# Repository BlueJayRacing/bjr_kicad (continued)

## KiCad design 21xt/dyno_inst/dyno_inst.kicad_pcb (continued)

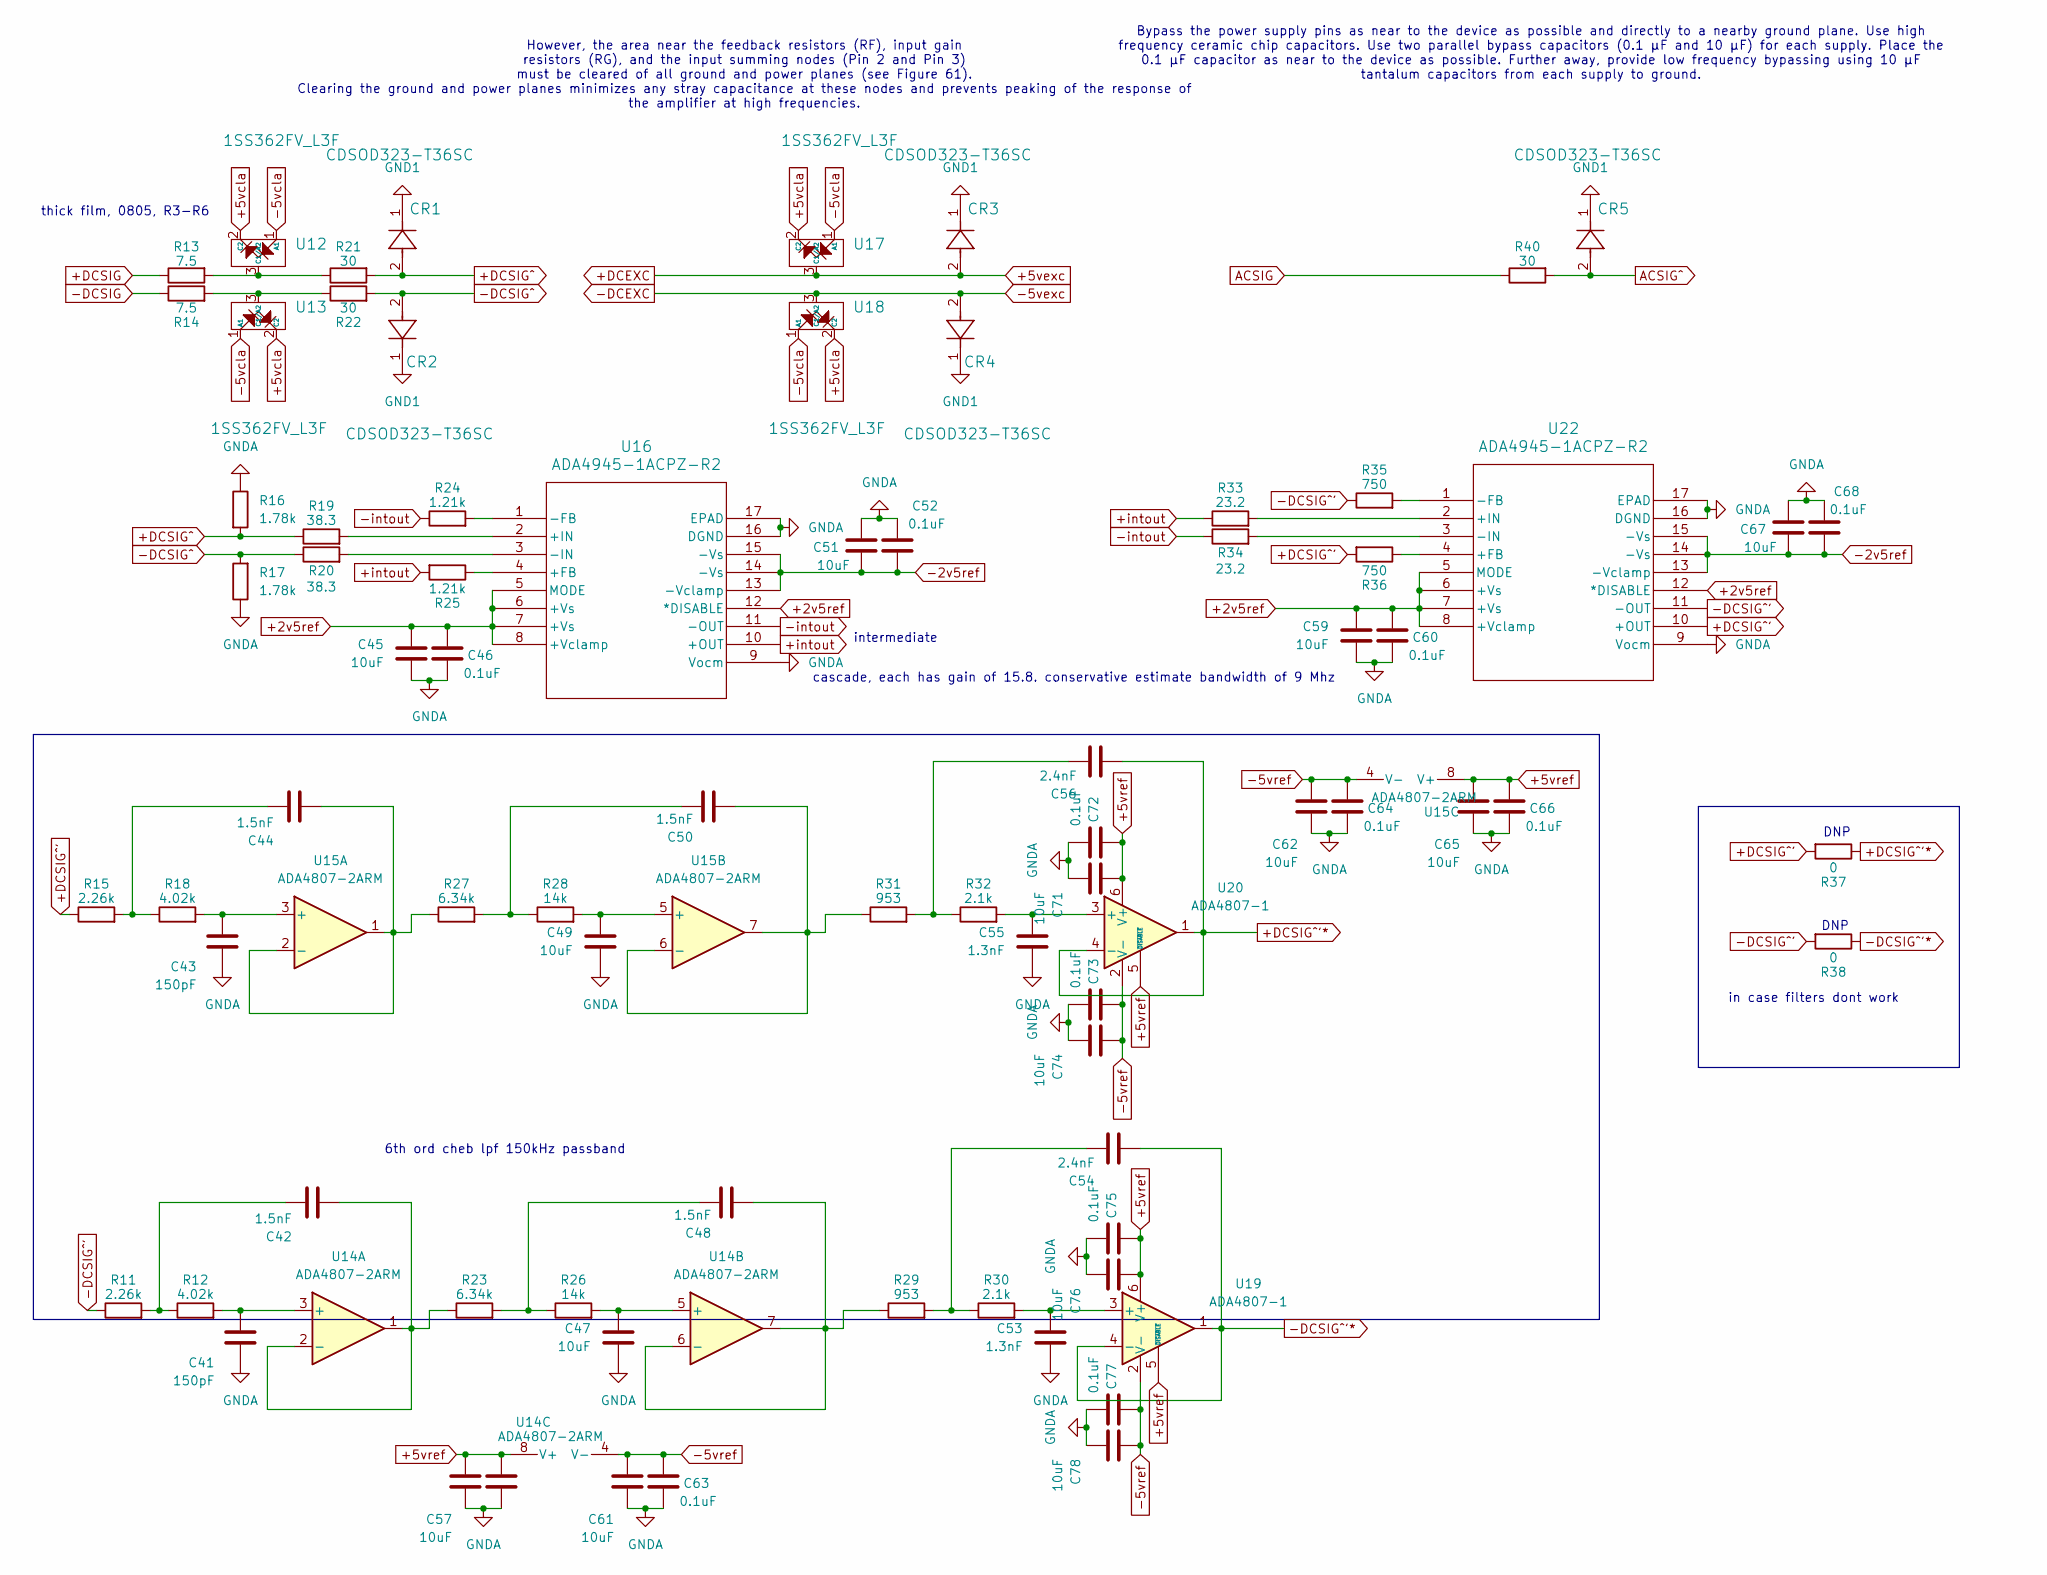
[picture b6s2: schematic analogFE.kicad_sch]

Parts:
C41, C43: 150pF; C_0402_1005Metric
C42, C44, C48, C50: 1.5nF; C_0402_1005Metric
C45, C47, C49, C51, C57, C59, C61, C62, C65, C67, C71, C74, C76, C78: 10uF; C_0402_1005Metric
C46, C52, C58, C60, C63, C64, C66, C68, C72, C73, C75, C77: 0.1uF; C_0402_1005Metric
C53, C55: 1.3nF; C_0402_1005Metric
C54, C56: 2.4nF; C_0402_1005Metric
CR1, CR2, CR3, CR4, CR5: CDSOD323-T36SC; DIODE_CDSOD323-T36SC_BRN
R11, R15: 2.26k; R_0402_1005Metric
R12, R18: 4.02k; R_0402_1005Metric
R13, R14: 7.5; R_0805_2012Metric
R16, R17: 1.78k; R_0402_1005Metric
R19, R20: 38.3; R_0402_1005Metric
R21, R22, R40: 30; R_0805_2012Metric
R23, R27: 6.34k; R_0402_1005Metric
R24, R25: 1.21k; R_0402_1005Metric
R26, R28: 14k; R_0402_1005Metric
R29, R31: 953; R_0402_1005Metric
R30, R32: 2.1k; R_0402_1005Metric
R33, R34: 23.2; R_0402_1005Metric
R35, R36: 750; R_0402_1005Metric
R37, R38: 0; R_0402_1005Metric
U12, U13, U17, U18: 1SS362FV_L3F; SOT-723
U14, U15: ADA4807-2ARM; MSOP-8_3x3mm_P0.65mm
U16, U22: ADA4945-1ACPZ-R2; LFCSP16_ADA4945-1ACPZ-R2_ADI
U19, U20: ADA4807-1; KS-6_ADI

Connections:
+2v5ref: C45.1, C46.1, C59.1, C60.1, U16.5 (MODE), U16.6 (+Vs), U16.7 (+Vs), U16.8 (+Vclamp), U16.12 (*DISABLE), U22.5 (MODE), U22.6 (+Vs), U22.7 (+Vs), U22.8 (+Vclamp), U22.12 (*DISABLE); also elsewhere on the board
+5vcla: U12.2 (C2), U13.2 (C2), U17.2 (C2), U18.2 (C2); also elsewhere on the board
+5vexc: CR3.2, U17.3 (C1/A2); also elsewhere on the board
+5vref: C57.1, C58.1, C65.1, C66.1, C71.1, C72.1, C75.1, C76.1, U14.8 (V+), U15.8 (V+), U19.5 (~DISABLE), U19.6 (V+), U20.5 (~DISABLE), U20.6 (V+); also elsewhere on the board
+DCSIG: R13.1; also elsewhere on the board
+DCSIG^: CR1.2, R16.2, R19.1, R21.2
+DCSIG^': R15.1, R36.2, R37.2, U22.10 (+OUT)
+DCSIG^'*: C56.2, R37.1, U20.1, U20.4 (-); also elsewhere on the board
+intout: R25.2, R33.1, U16.10 (+OUT)
-2v5ref: C51.2, C52.2, C67.2, C68.2, U16.13 (-Vclamp), U16.14 (-Vs), U16.15 (-Vs), U22.13 (-Vclamp), U22.14 (-Vs), U22.15 (-Vs); also elsewhere on the board
-5vcla: U12.1 (A1), U13.1 (A1), U17.1 (A1), U18.1 (A1); also elsewhere on the board
-5vexc: CR4.2, U18.3 (C1/A2); also elsewhere on the board
-5vref: C61.1, C62.1, C63.1, C64.1, C73.1, C74.1, C77.1, C78.1, U14.4 (V-), U15.4 (V-), U19.2 (V-), U20.2 (V-); also elsewhere on the board
-DCSIG: R14.1; also elsewhere on the board
-DCSIG^: CR2.2, R17.2, R20.1, R22.2
-DCSIG^': R11.1, R35.1, R38.2, U22.11 (-OUT)
-DCSIG^'*: C54.2, R38.1, U19.1, U19.4 (-); also elsewhere on the board
-intout: R24.1, R34.1, U16.11 (-OUT)
ACSIG: R40.1; also elsewhere on the board
ACSIG^: CR5.2, R40.2; also elsewhere on the board
GND1: CR1.1, CR2.1, CR3.1, CR4.1, CR5.1; also elsewhere on the board
GNDA: C41.2, C43.2, C45.2, C46.2, C47.2, C49.2, C51.1, C52.1, C53.2, C55.2, C57.2, C58.2, C59.2, C60.2, C61.2, C62.2, C63.2, C64.2, C65.2, C66.2, C67.1, C68.1, C71.2, C72.2, C73.2, C74.2, C75.2, C76.2, C77.2, C78.2, R16.1, R17.1, U16.9 (Vocm), U16.16 (DGND), U16.17 (EPAD), U22.9 (Vocm), U22.16 (DGND), U22.17 (EPAD); also elsewhere on the board
unnamed: C42.1, R11.2, R12.1
unnamed: C44.1, R15.2, R18.1
unnamed: C48.1, R23.2, R26.1
unnamed: C50.1, R27.2, R28.1
unnamed: C54.1, R29.2, R30.1
unnamed: C56.1, R31.2, R32.1
unnamed: R13.2, R21.1, U12.3 (C1/A2)
unnamed: R14.2, R22.1, U13.3 (C1/A2)
unnamed: C41.1, R12.2, U14.3 (+)
unnamed: C42.2, R23.1, U14.1, U14.2 (-)
unnamed: C47.1, R26.2, U14.5 (+)
unnamed: C48.2, R29.1, U14.6 (-), U14.7
unnamed: C43.1, R18.2, U15.3 (+)
unnamed: C44.2, R27.1, U15.1, U15.2 (-)
unnamed: C49.1, R28.2, U15.5 (+)
unnamed: C50.2, R31.1, U15.6 (-), U15.7
unnamed: R25.1, U16.4 (+FB)
unnamed: R19.2, U16.2 (+IN)
unnamed: R24.2, U16.1 (-FB)
unnamed: R20.2, U16.3 (-IN)
unnamed: C53.1, R30.2, U19.3 (+)
unnamed: C55.1, R32.2, U20.3 (+)
unnamed: R36.1, U22.4 (+FB)
unnamed: R33.2, U22.2 (+IN)
unnamed: R35.2, U22.1 (-FB)
unnamed: R34.2, U22.3 (-IN)

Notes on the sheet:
in case filters dont work
DNP
intermediate
6th ord cheb lpf 150kHz passband
However, the area near the feedback resistors (RF), input gain resistors (RG), and the input summing nodes (Pin 2 and Pin 3) must be cleared of all ground and power planes (see Figure 61). Clearing the ground and power planes minimizes any stray capacitance at these nodes and prevents peaking of th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
Bypass the power supply pins as near to the device as possible and directly to a nearby ground plane. Use high frequency ceramic chip capacitors. Use two parallel bypass capacitors (0.1 µF and 10 µF) for each supply. Place the 0.1 µF capacitor as near to the device as possible. Further away, provid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
thick film, 0805, R3-R6
cascade, each has gain of 15.8. conservative estimate bandwidth of 9 Mhz

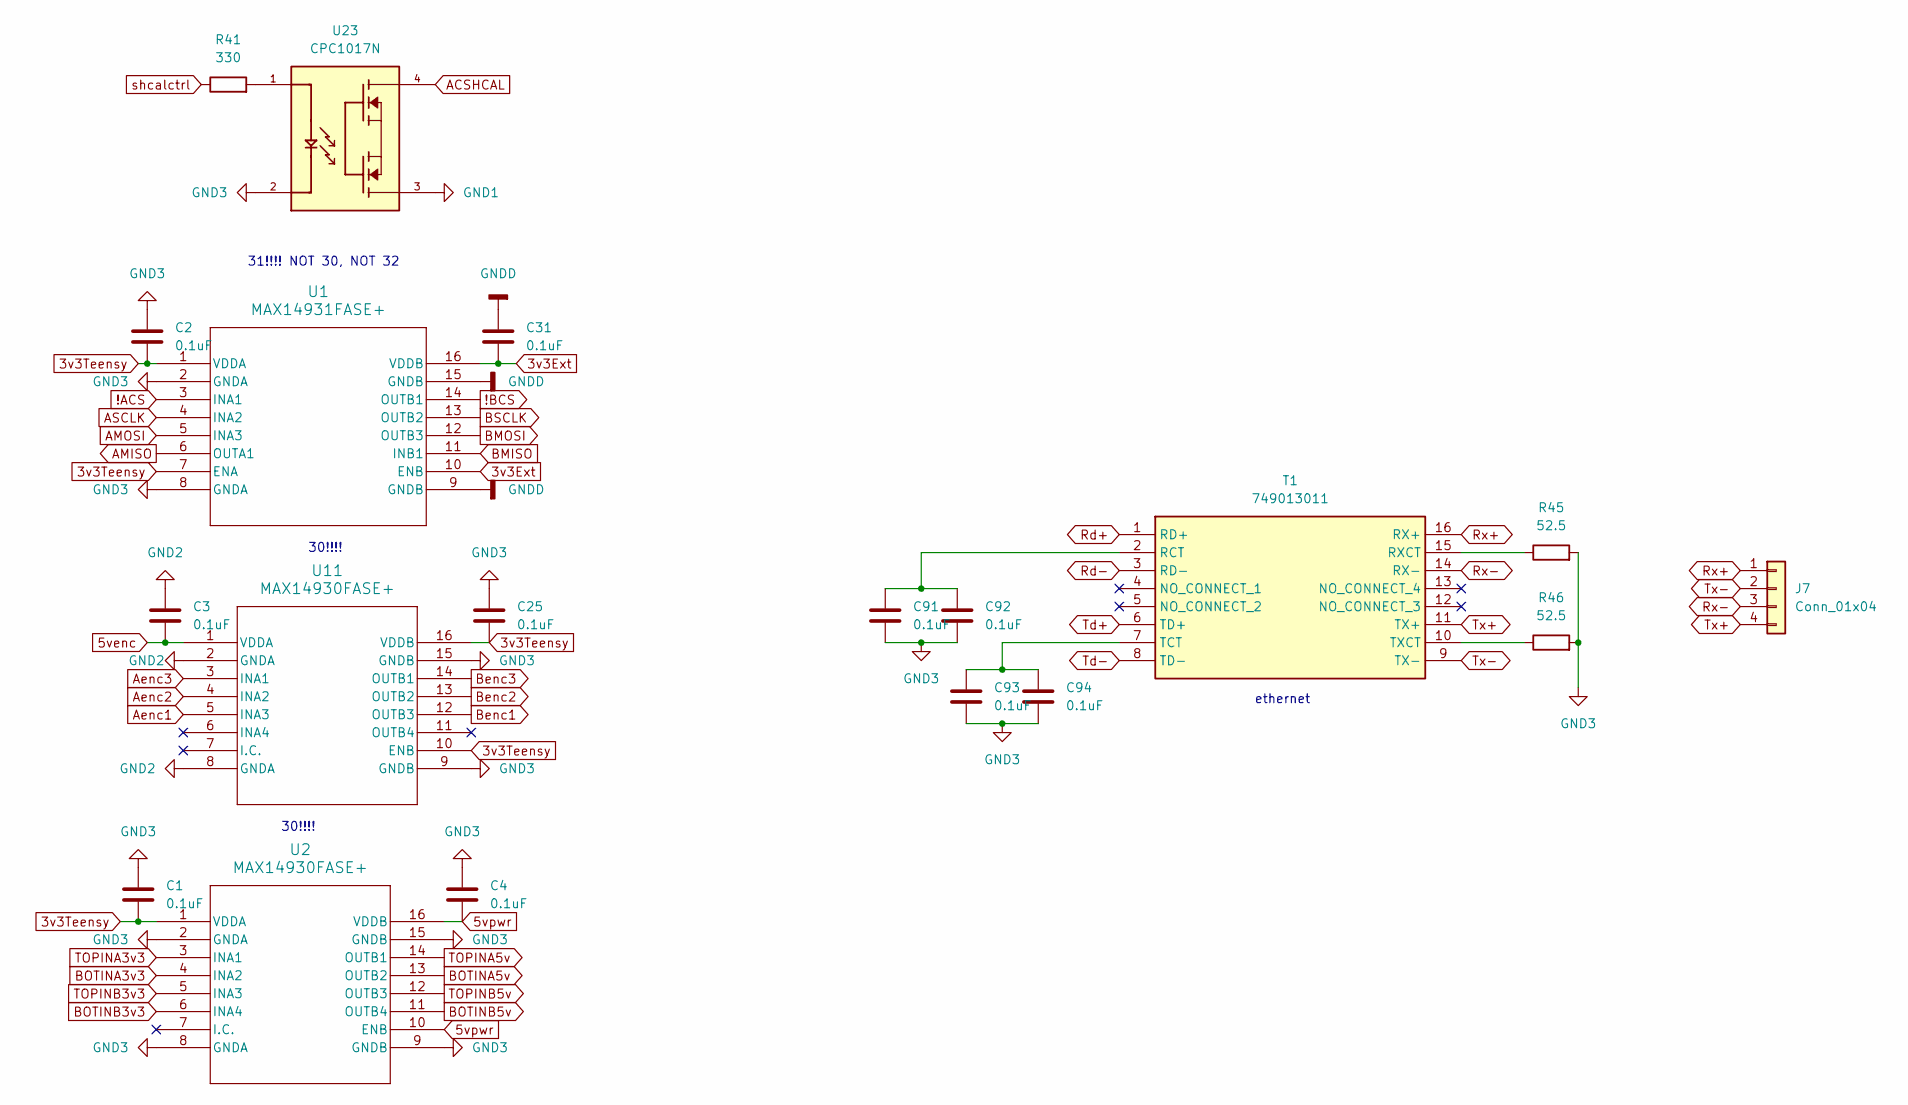
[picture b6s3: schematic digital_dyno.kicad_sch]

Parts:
C1, C2, C3, C4, C25, C31, C91, C92, C93, C94: 0.1uF; C_0402_1005Metric
J7: Conn_01x04; CONN_T4041017041-000_TEC
R41: 330; R_0402_1005Metric
R45, R46: 52.5; R_0402_1005Metric
T1: 749013011; Mouser Part Number 710-749013011
U1: MAX14931FASE+; 21-0041_S16&plus_1_MXM_1
U2, U11: MAX14930FASE+; 21-0041_S16&plus_1_MXM
U23: CPC1017N; SOIC254P610X218-4N

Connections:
3v3Ext: C31.2, U1.10 (ENB), U1.16 (VDDB); also elsewhere on the board
3v3Teensy: C1.2, C2.2, C25.2, U1.1 (VDDA), U1.7 (ENA), U2.1 (VDDA), U11.10 (ENB), U11.16 (VDDB); also elsewhere on the board
5venc: C3.2, U11.1 (VDDA); also elsewhere on the board
5vpwr: C4.2, U2.10 (ENB), U2.16 (VDDB); also elsewhere on the board
!ACS: U1.3 (INA1); also elsewhere on the board
!BCS: U1.14 (OUTB1); also elsewhere on the board
ACSHCAL: U23.4; also elsewhere on the board
AMISO: U1.6 (OUTA1); also elsewhere on the board
AMOSI: U1.5 (INA3); also elsewhere on the board
ASCLK: U1.4 (INA2); also elsewhere on the board
Aenc1: U11.5 (INA3); also elsewhere on the board
Aenc2: U11.4 (INA2); also elsewhere on the board
Aenc3: U11.3 (INA1); also elsewhere on the board
BMISO: U1.11 (INB1); also elsewhere on the board
BMOSI: U1.12 (OUTB3); also elsewhere on the board
BOTINA3v3: U2.4 (INA2); also elsewhere on the board
BOTINA5v: U2.13 (OUTB2); also elsewhere on the board
BOTINB3v3: U2.6 (INA4); also elsewhere on the board
BOTINB5v: U2.11 (OUTB4); also elsewhere on the board
BSCLK: U1.13 (OUTB2); also elsewhere on the board
Benc1: U11.12 (OUTB3); also elsewhere on the board
Benc2: U11.13 (OUTB2); also elsewhere on the board
Benc3: U11.14 (OUTB1); also elsewhere on the board
GND1: U23.3; also elsewhere on the board
GND2: C3.1, U11.2 (GNDA), U11.8 (GNDA); also elsewhere on the board
GND3: C1.1, C2.1, C4.1, C25.1, C91.2, C92.2, C93.2, C94.2, R45.2, R46.2, U1.2 (GNDA), U1.8 (GNDA), U2.2 (GNDA), U2.8 (GNDA), U2.9 (GNDB), U2.15 (GNDB), U11.9 (GNDB), U11.15 (GNDB), U23.2; also elsewhere on the board
GNDD: C31.1, U1.9 (GNDB), U1.15 (GNDB); also elsewhere on the board
unnamed: R41.2, U23.1
unnamed: C91.1, C92.1, T1.2 (RCT)
unnamed: R45.1, T1.15 (RXCT)
unnamed: C93.1, C94.1, T1.7 (TCT)
unnamed: R46.1, T1.10 (TXCT)
Rd+: T1.1 (RD+); also elsewhere on the board
Rd-: T1.3 (RD-); also elsewhere on the board
Rx+: J7.1, T1.16 (RX+)
Rx-: J7.3, T1.14 (RX-)
TOPINA3v3: U2.3 (INA1); also elsewhere on the board
TOPINA5v: U2.14 (OUTB1); also elsewhere on the board
TOPINB3v3: U2.5 (INA3); also elsewhere on the board
TOPINB5v: U2.12 (OUTB3); also elsewhere on the board
Td+: T1.6 (TD+); also elsewhere on the board
Td-: T1.8 (TD-); also elsewhere on the board
Tx+: J7.4, T1.11 (TX+)
Tx-: J7.2, T1.9 (TX-)
shcalctrl: R41.1; also elsewhere on the board

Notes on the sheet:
31!!!! NOT 30, NOT 32
30!!!!
ethernet

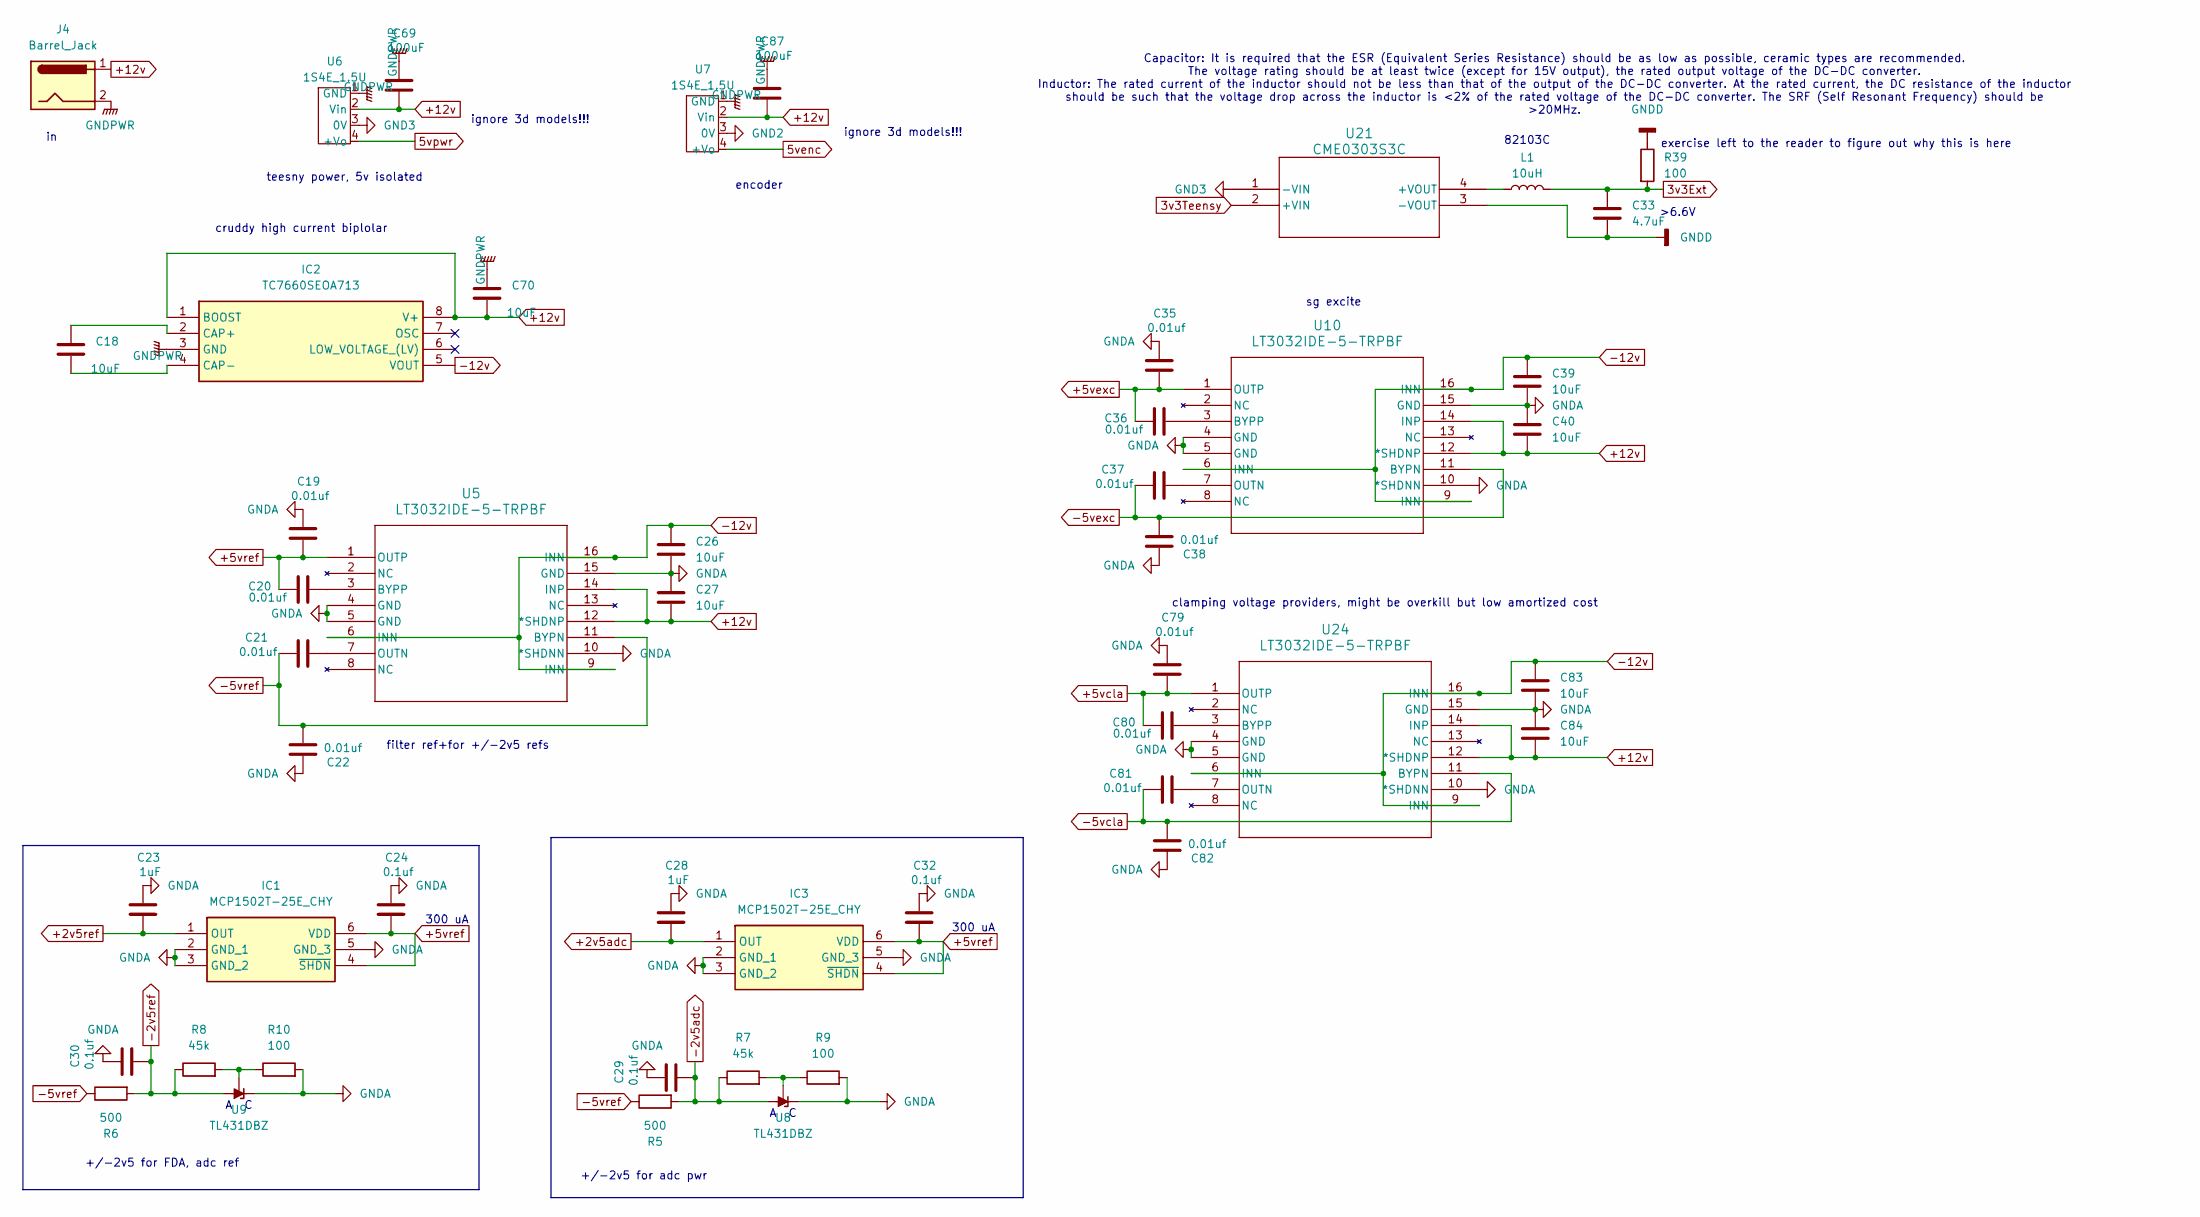
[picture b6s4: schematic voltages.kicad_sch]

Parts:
C18, C70: 10uF; C_0603_1608Metric
C19, C20, C21, C22, C35, C36, C37, C38, C79, C80, C81, C82: 0.01uf; C_0402_1005Metric
C23, C28: 1uF; C_0402_1005Metric
C24, C29, C30, C32: 0.1uf; C_0402_1005Metric
C26, C27, C39, C40, C83, C84: 10uF; C_0402_1005Metric
C33: 4.7uF; C_0402_1005Metric
C69, C87: 100uF; C_0805_2012Metric
IC1, IC3: MCP1502T-25E_CHY; SOT95P280X145-6N; Mouser Part Number 579-MCP1502T-50E/CHY
IC2: TC7660SEOA713; SOIC127P600X175-8N; Mouser Part Number 579-TC7660SEOA713
J4: Barrel_Jack; CUI_PJ-037A
L1: 10uH; L_1210_3225Metric
R5, R6: 500; R_0402_1005Metric
R7, R8: 45k; R_0402_1005Metric
R9, R10, R39: 100; R_0402_1005Metric
U5, U10, U24: LT3032IDE-5-TRPBF; DFN14_DE14MA_ADI
U6, U7: 1S4E_1.5U; PinHeader_1x04_P2.54mm_Vertical
U8, U9: TL431DBZ; SOT-23
U21: CME0303S3C; SIP4_CME0303_MUR

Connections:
3v3Ext: C33.1, L1.2, R39.2; also elsewhere on the board
3v3Teensy: U21.2 (+VIN); also elsewhere on the board
5venc: U7.4 (+Vo); also elsewhere on the board
5vpwr: U6.4 (+Vo); also elsewhere on the board
+2v5adc: C28.2, IC3.1 (OUT); also elsewhere on the board
+2v5ref: C23.2, IC1.1 (OUT); also elsewhere on the board
+5vcla: C79.2, C80.1, U24.1 (OUTP); also elsewhere on the board
+5vexc: C35.2, C36.1, U10.1 (OUTP); also elsewhere on the board
+5vref: C19.2, C20.1, C24.2, C32.2, IC1.4 (~SHDN), IC1.6 (VDD), IC3.4 (~SHDN), IC3.6 (VDD), U5.1 (OUTP); also elsewhere on the board
+12v: C27.2, C40.2, C69.2, C70.2, C84.2, C87.2, IC2.1 (BOOST), IC2.8 (V+), J4.1, U5.12 (*SHDNP), U5.14 (INP), U6.2 (Vin), U7.2 (Vin), U10.12 (*SHDNP), U10.14 (INP), U24.12 (*SHDNP), U24.14 (INP)
-2v5adc: C29.2, R5.2, R7.1, U8.3 (A); also elsewhere on the board
-2v5ref: C30.2, R6.2, R8.1, U9.3 (A); also elsewhere on the board
-5vcla: C81.1, C82.2, U24.11 (BYPN); also elsewhere on the board
-5vexc: C37.1, C38.2, U10.11 (BYPN); also elsewhere on the board
-5vref: C21.1, C22.2, R5.1, R6.1, U5.11 (BYPN); also elsewhere on the board
-12v: C26.1, C39.1, C83.1, IC2.5 (VOUT), U5.6 (INN), U5.9 (INN), U5.16 (INN), U10.6 (INN), U10.9 (INN), U10.16 (INN), U24.6 (INN), U24.9 (INN), U24.16 (INN)
GND2: U7.3 (0V); also elsewhere on the board
GND3: U6.3 (0V), U21.1 (-VIN); also elsewhere on the board
GNDA: C19.1, C22.1, C23.1, C24.1, C26.2, C27.1, C28.1, C29.1, C30.1, C32.1, C35.1, C38.1, C39.2, C40.1, C79.1, C82.1, C83.2, C84.1, IC1.2 (GND_1), IC1.3 (GND_2), IC1.5 (GND_3), IC3.2 (GND_1), IC3.3 (GND_2), IC3.5 (GND_3), R9.2, R10.2, U5.4 (GND), U5.5 (GND), U5.10 (*SHDNN), U5.15 (GND), U8.1 (K), U9.1 (K), U10.4 (GND), U10.5 (GND), U10.10 (*SHDNN), U10.15 (GND), U24.4 (GND), U24.5 (GND), U24.10 (*SHDNN), U24.15 (GND); also elsewhere on the board
GNDD: C33.2, R39.1, U21.3 (-VOUT); also elsewhere on the board
GNDPWR: C69.1, C70.1, C87.1, IC2.3 (GND), J4.2, U6.1 (GND), U7.1 (GND); also elsewhere on the board
unnamed: C18.1, IC2.2 (CAP+)
unnamed: C18.2, IC2.4 (CAP-)
unnamed: C20.2, U5.3 (BYPP)
unnamed: C21.2, U5.7 (OUTN)
unnamed: R7.2, R9.1, U8.2 (REF)
unnamed: R8.2, R10.1, U9.2 (REF)
unnamed: C36.2, U10.3 (BYPP)
unnamed: C37.2, U10.7 (OUTN)
unnamed: L1.1, U21.4 (+VOUT)
unnamed: C80.2, U24.3 (BYPP)
unnamed: C81.2, U24.7 (OUTN)

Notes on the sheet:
cruddy high current biplolar
clamping voltage providers, might be overkill but low amortized cost
exercise left to the reader to figure out why this is here
encoder
Capacitor: It is required that the ESR (Equivalent Series Resistance) should be as low as possible, ceramic types are recommended. The voltage rating should be at least twice (except for 15V output), the rated output voltage of the DC-DC converter. Inductor: The rated current of the inductor should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
ignore 3d models!!!
+/-2v5 for adc pwr
300 uA
+/-2v5 for FDA, adc ref
filter ref+for +/-2v5 refs
teesny power, 5v isolated
A C
>6.6V
sg excite
82103C

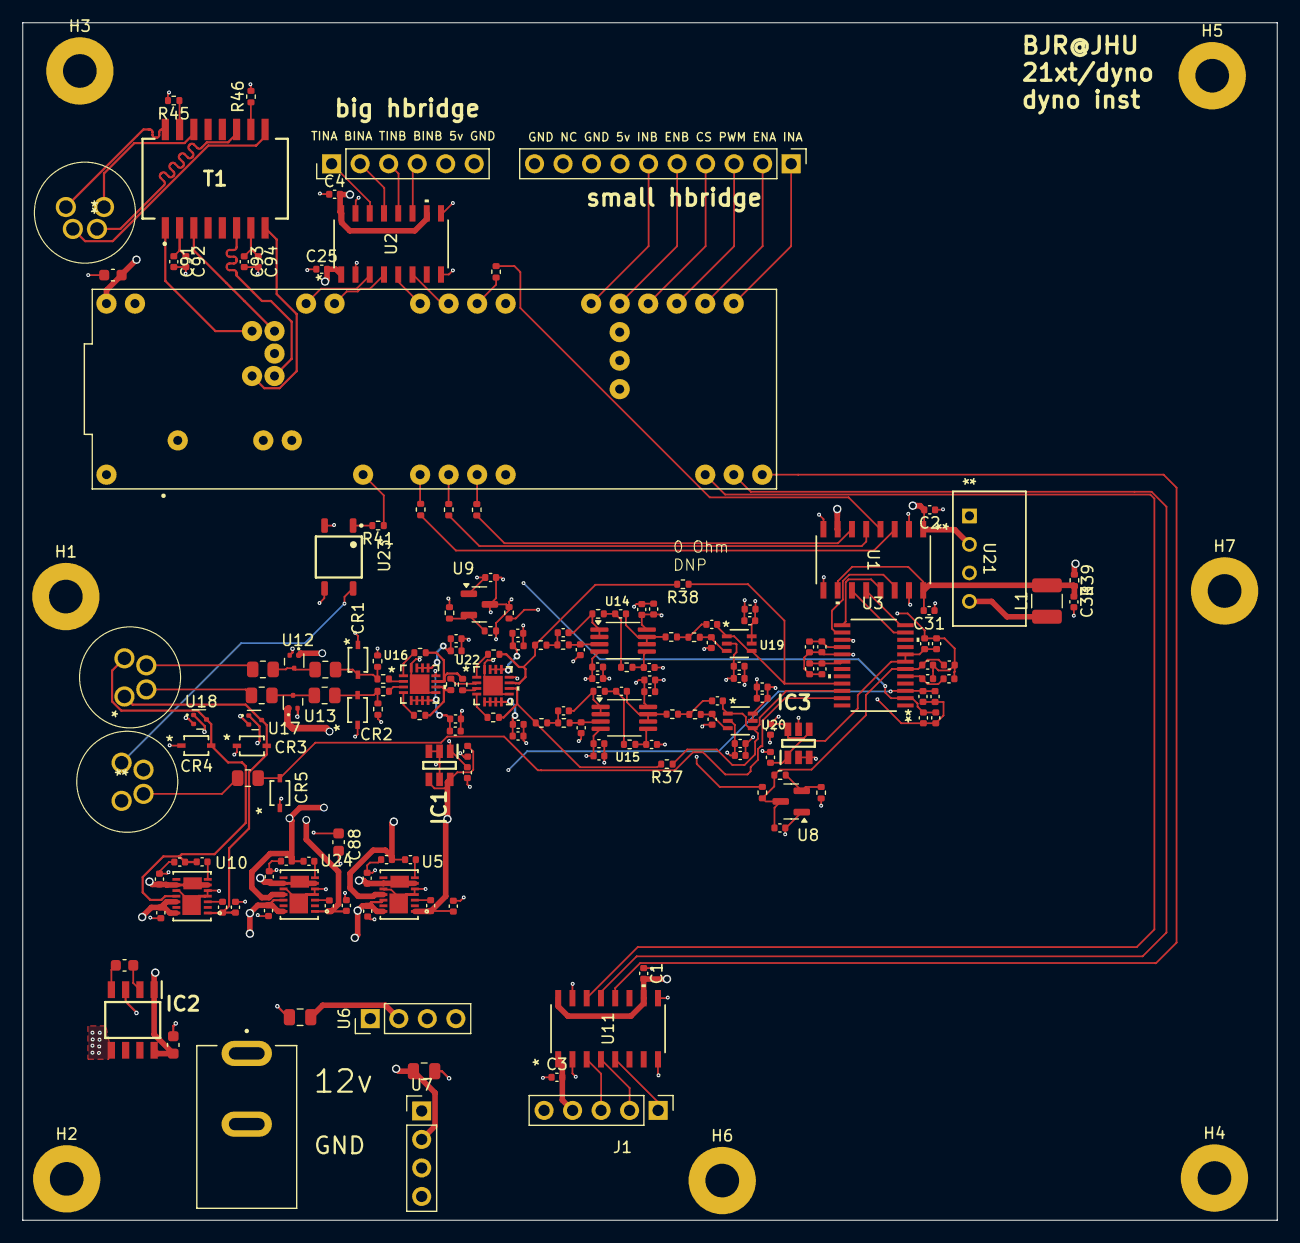
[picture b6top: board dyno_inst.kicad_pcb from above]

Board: 4 copper layers, 111.8 x 106.7 mm, 182 parts (0 on the bottom side), 121 nets.
